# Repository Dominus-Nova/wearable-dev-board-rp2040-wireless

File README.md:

# wearable-dev-board-rp2040-wireless
E

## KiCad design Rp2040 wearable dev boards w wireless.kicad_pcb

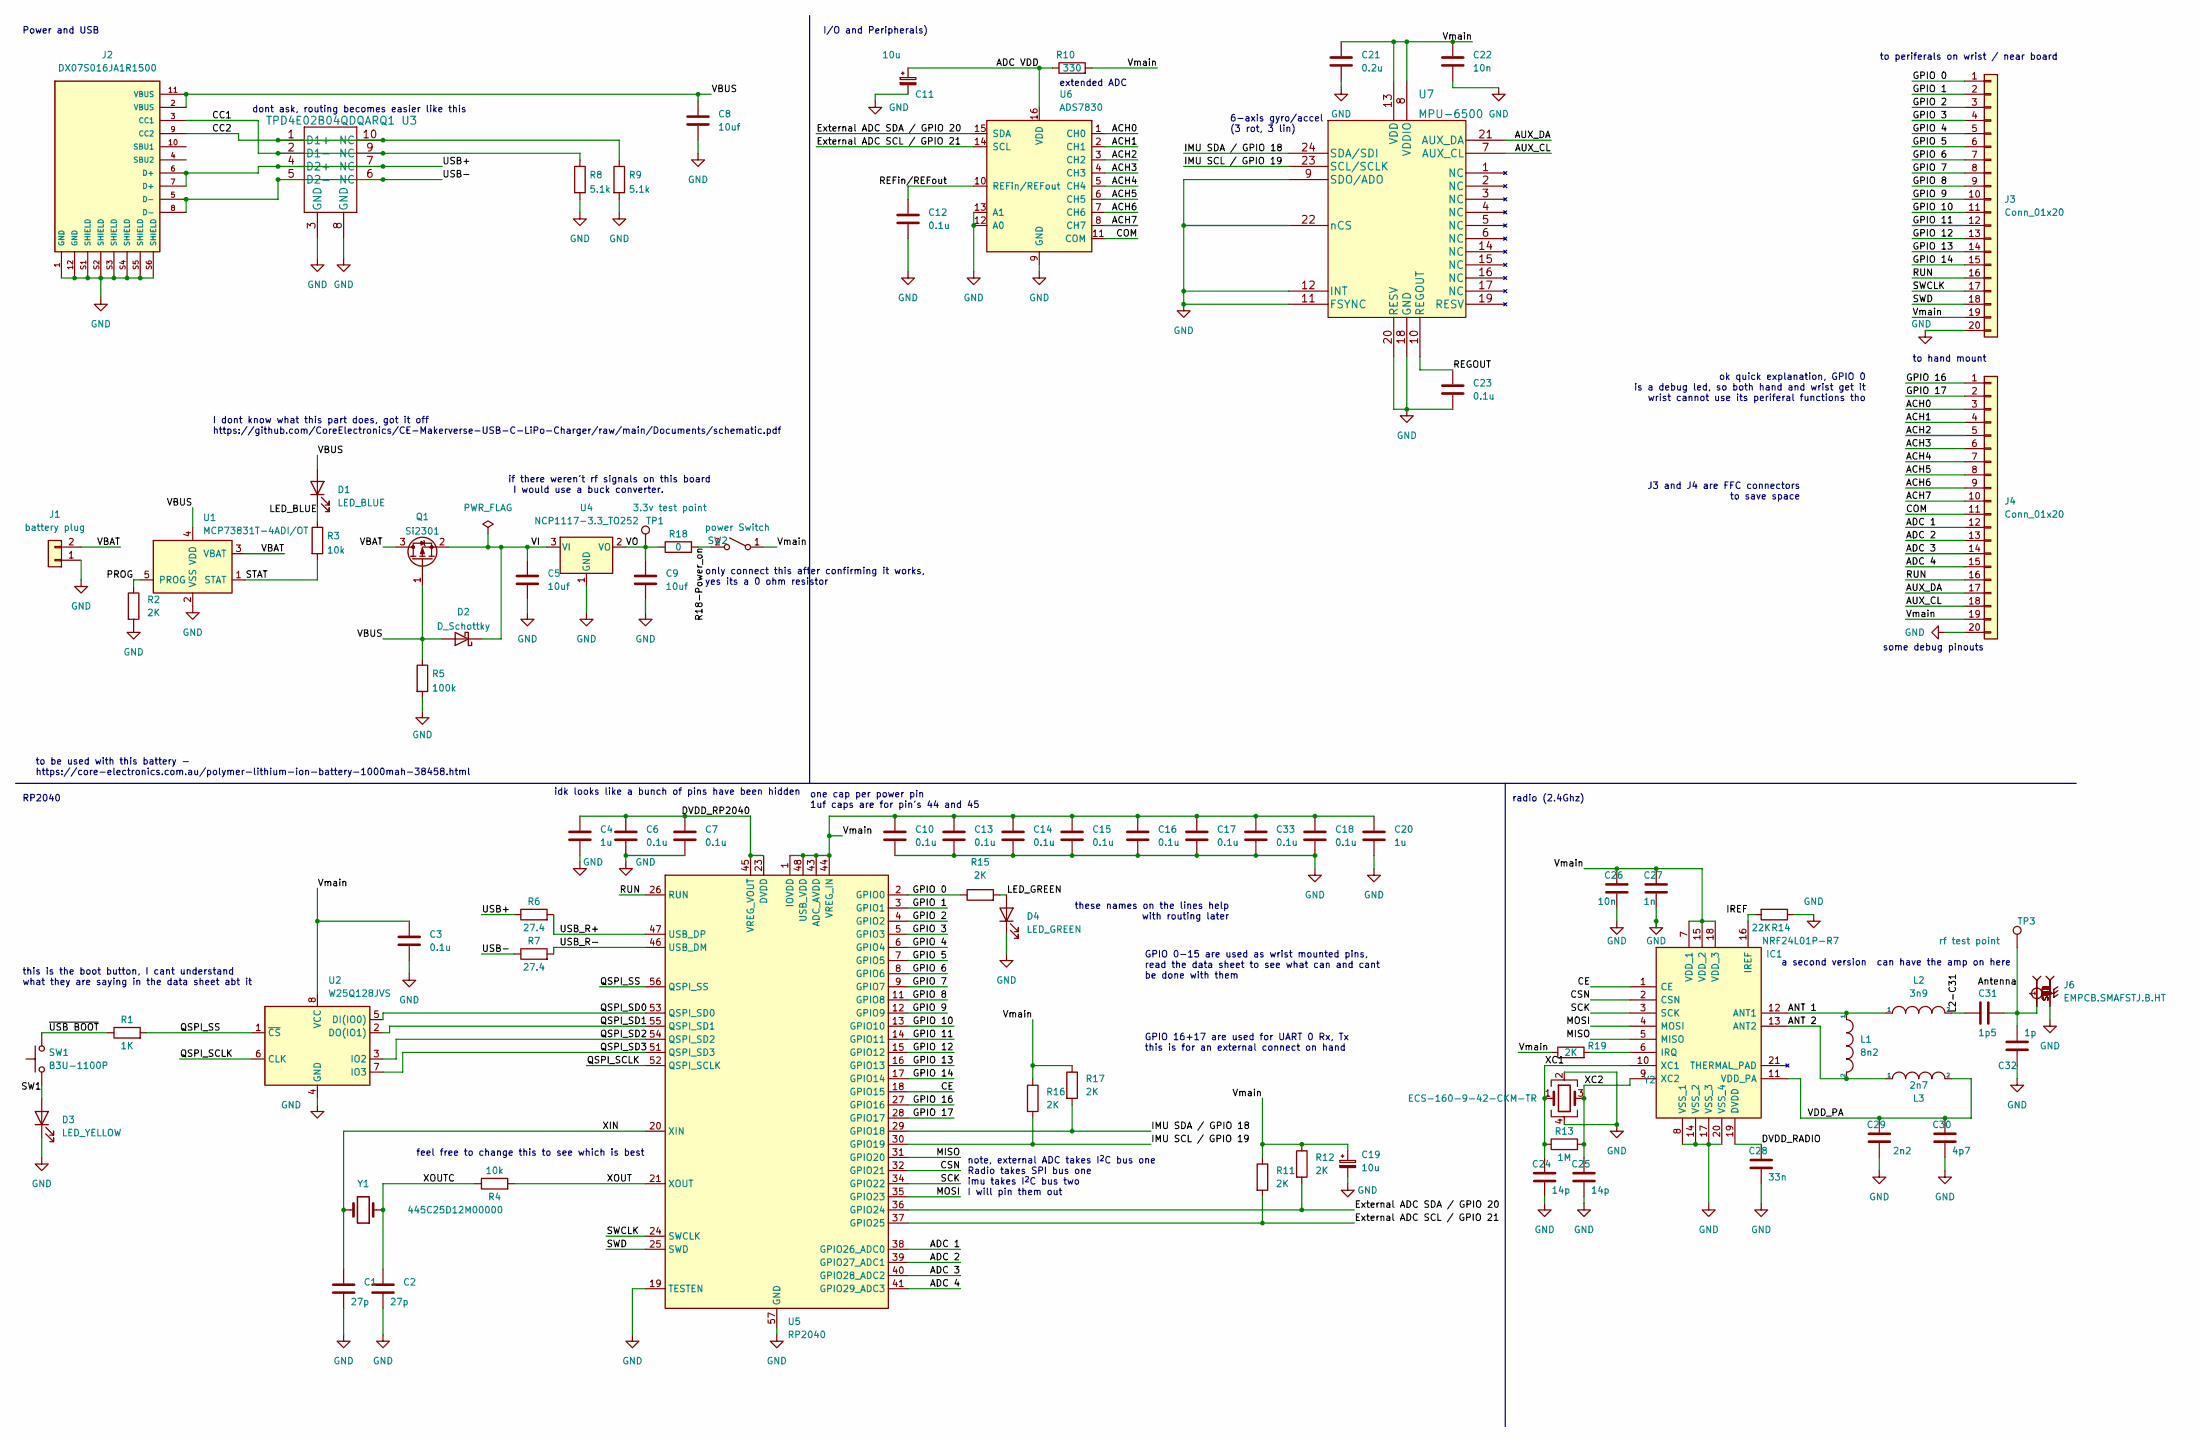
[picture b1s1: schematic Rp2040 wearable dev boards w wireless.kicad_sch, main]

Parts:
C1, C2: 27p; C_01005_0402Metric; Digikey Part Number 445-7173-6-ND
C3, C6, C7, C10, C12, C13, C14, C15, C16, C17, C18, C23, C33: 0.1u; C_0201_0603Metric; Digikey Part Number 490-3167-1-ND
C4, C20: 1u; C_0201_0603Metric; Digikey Part Number 478-7862-1-ND
C5, C8, C9: 10uf; C_0402_1005Metric; Digikey Part Number 490-GRM155R60J106ME05JCT-ND
C11, C19: 10u; CP_Elec_5x5.3; Digikey Part Number 732-6416-6-ND
C21: 0.2u; C_1206_3216Metric; Digikey Part Number 478-12814-1-ND
C22, C26: 10n; C_01005_0402Metric; Digikey Part Number 490-13319-1-ND
C24, C25: 14p; C_0402_1005Metric; Digikey Part Number 490-GJM1555C1H140FB01DCT-ND
C27: 1n; C_01005_0402Metric; Digikey Part Number 490-GRM022R71C102KE14LCT-ND
C28: 33n; C_01005_0402Metric; Digikey Part Number 490-9977-1-ND
C29: 2n2; C_01005_0402Metric; Digikey Part Number 490-7164-1-ND
C30: 4p7; C_01005_0402Metric; Digikey Part Number 490-13585-1-ND
C31: 1p5; C_01005_0402Metric; Digikey Part Number 490-13488-1-ND
C32: 1p; C_01005_0402Metric; Digikey Part Number 490-13474-1-ND
D1: LED_BLUE; LED_0603_1608Metric; Digikey Part Number 160-1827-1-ND
D2: D_Schottky; D_SMA; Digikey Part Number 641-1690-1-ND
D3: LED_YELLOW; LED_0603_1608Metric; Digikey Part Number 160-1448-1-ND
D4: LED_GREEN; LED_0603_1608Metric; Digikey Part Number 160-1446-1-ND
IC1: NRF24L01P-R7; QFN50P400X400X95-21N-D; Manufacturer_Part_Number NRF24L01P-R7; Mouser Part Number 949-NRF24L01P-R7
J1: battery plug; JST_PH_S2B-PH-SM4-TB_1x02-1MP_P2.00mm_Horizontal; Digikey Part Number 455-1749-1-ND
J2: DX07S016JA1R1500; JAE_DX07S016JA1R1500; PARTREV 1; Digikey Part Number 670-DX07S016JA1R1500CT-ND
J3, J4: Conn_01x20; TE_2-84952-0_1x20-1MP_P1.0mm_Horizontal; Digikey Part Number A100319CT-ND
J6: EMPCB.SMAFSTJ.B.HT; TAOGLAS_EMPCB.SMAFSTJ.B.HT; Digikey Part Number 931-1175-ND
L1: 8n2; L_0402_1005Metric; Digikey Part Number 490-6849-1-ND
L2: 3n9; L_0402_1005Metric; Digikey Part Number 490-6813-1-ND
L3: 2n7; L_0402_1005Metric; Digikey Part Number 490-6799-1-ND
Q1: Si2301; SOT-23; Digikey Part Number 353-SI2301A-TPCT-ND
R1: 1K; R_0402_1005Metric; Digikey Part Number 311-1.0KJRCT-ND
R2, R11, R12, R15, R16, R17, R19: 2K; R_0402_1005Metric; Digikey Part Number YAG2303CT-ND
R3, R4: 10k; R_0402_1005Metric; Digikey Part Number 311-10KJRCT-ND
R5: 100k; R_0402_1005Metric; Digikey Part Number 13-RC0402FR-13100KLCT-ND
R6, R7: 27.4; R_0402_1005Metric; Digikey Part Number YAG3085CT-ND
R8, R9: 5.1k; R_0402_1005Metric; Digikey Part Number 13-RC0402FR-135K1LCT-ND
R10: 330; R_0402_1005Metric; Digikey Part Number 311-330JRCT-ND
R13: 1M; R_0402_1005Metric; Digikey Part Number 311-1.0MJRCT-ND
R14: 22K; R_0402_1005Metric; Digikey Part Number 311-22.0KLRCT-ND
R18: 0; R_0402_1005Metric; Digikey Part Number 311-0.0LRCT-ND
SW1: B3U-1100P; SW_SPST_B3U-1100P; Digikey Part Number SW1021CT-ND
SW2: power Switch; JST_PH_S2B-PH-SM4-TB_1x02-1MP_P2.00mm_Horizontal; Digikey Part Number 455-1749-1-ND
TP1: 3.3v test point; TestPoint_Pad_D2.0mm; Digikey Part Number n/a
TP3: rf test point; TestPoint_Pad_D2.0mm; Digikey Part Number n/a
U1: MCP73831T-4ADI/OT; SOT-23-5; Digikey Part Number MCP73831T-4ADI/OTCT-ND
U2: W25Q128JVS; SOIC-8_5.23x5.23mm_P1.27mm; Digikey Part Number W25Q128JVSIMCT-ND
U3: TPD4E02B04QDQARQ1; Digikey Part Number 296-48995-1-ND
U4: NCP1117-3.3_TO252; SOT-223; Digikey Part Number NCP1117LPST33T3GOSCT-ND
U5: RP2040; QFN-56-1EP_7x7mm_P0.4mm_EP3.2x3.2mm; Digikey Part Number 2648-SC0914(13)CT-ND
U6: ADS7830; TSSOP-16_4.4x5mm_P0.65mm; Digikey Part Number 296-25899-1-ND
U7: MPU-6500; Digikey Part Number 1428-1011-1-ND
Y1: 445C25D12M00000; Crystal_SMD_5032-2Pin_5.0x3.2mm_HandSoldering; Digikey Part Number CTX1162CT-ND
Y2: ECS-160-9-42-CKM-TR; XTAL_ECS-160-9-42-CKM-TR; Digikey Part Number XC1611CT-ND

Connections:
/ACH0: J4.3, U6.1 (CH0)
/ACH1: J4.4, U6.2 (CH1)
/ACH2: J4.5, U6.3 (CH2)
/ACH3: J4.6, U6.4 (CH3)
/ACH4: J4.7, U6.5 (CH4)
/ACH5: J4.8, U6.6 (CH5)
/ACH6: J4.9, U6.7 (CH6)
/ACH7: J4.10, U6.8 (CH7)
/ADC 1: J4.12, U5.38 (GPIO26_ADC0)
/ADC 2: J4.13, U5.39 (GPIO27_ADC1)
/ADC 3: J4.14, U5.40 (GPIO28_ADC2)
/ADC 4: J4.15, U5.41 (GPIO29_ADC3)
/ADC VDD: C11.1, R10.1, U6.16 (VDD)
/ANT 1: IC1.12 (ANT1), L1.1, L2.1
/ANT 2: IC1.13 (ANT2), L1.2, L3.1
/AUX_CL: J4.18, U7.7 (AUX_CL)
/AUX_DA: J4.17, U7.21 (AUX_DA)
/Antenna: C31.2, C32.1, J6.1, TP3.1; also elsewhere on the board
/CC1: J2.3 (CC1), R8.1, U3.2 (D1-), U3.9 (NC)
/CC2: J2.9 (CC2), R9.1, U3.1 (D1+), U3.10 (NC)
/CE: IC1.1 (CE), U5.18 (GPIO15)
/COM: J4.11, U6.11 (COM)
/CSN: IC1.2 (CSN), U5.32 (GPIO21)
/DVDD_RADIO: C28.1, IC1.19 (DVDD)
/DVDD_RP2040: C4.1, C6.1, C7.1, U5.23 (DVDD), U5.45 (VREG_VOUT), U5.50 (DVDD)
/External ADC SCL / GPIO 21: R11.2, U5.37 (GPIO25), U6.14 (SCL)
/External ADC SDA / GPIO 20: R12.2, U5.36 (GPIO24), U6.15 (SDA)
/GPIO 0: J3.1, R15.1, U5.2 (GPIO0)
/GPIO 1: J3.2, U5.3 (GPIO1)
/GPIO 2: J3.3, U5.4 (GPIO2)
/GPIO 3: J3.4, U5.5 (GPIO3)
/GPIO 4: J3.5, U5.6 (GPIO4)
/GPIO 5: J3.6, U5.7 (GPIO5)
/GPIO 6: J3.7, U5.8 (GPIO6)
/GPIO 7: J3.8, U5.9 (GPIO7)
/GPIO 8: J3.9, U5.11 (GPIO8)
/GPIO 9: J3.10, U5.12 (GPIO9)
/GPIO 10: J3.11, U5.13 (GPIO10)
/GPIO 11: J3.12, U5.14 (GPIO11)
/GPIO 12: J3.13, U5.15 (GPIO12)
/GPIO 13: J3.14, U5.16 (GPIO13)
/GPIO 14: J3.15, U5.17 (GPIO14)
/GPIO 16: J4.1, U5.27 (GPIO16)
/GPIO 17: J4.2, U5.28 (GPIO17)
/IMU SCL / GPIO 19: R16.2, U5.30 (GPIO19), U7.23 (SCL/SCLK)
/IMU SDA / GPIO 18: R17.2, U5.29 (GPIO18), U7.24 (SDA/SDI)
/IREF: IC1.16 (IREF), R14.2
/L2-C31: C31.1, L2.2
/LED_BLUE: D1.1 (K), R3.1
/LED_GREEN: D4.2 (A), R15.2
/MISO: IC1.5 (MISO), U5.31 (GPIO20)
/MOSI: IC1.4 (MOSI), U5.35 (GPIO23)
/PROG: R2.1, U1.5 (PROG)
/QSPI_SCLK: U2.6 (CLK), U5.52 (QSPI_SCLK)
/QSPI_SD0: U2.5 (DI(IO0)), U5.53 (QSPI_SD0)
/QSPI_SD1: U2.2 (DO(IO1)), U5.55 (QSPI_SD1)
/QSPI_SD2: U2.3 (IO2), U5.54 (QSPI_SD2)
/QSPI_SD3: U2.7 (IO3), U5.51 (QSPI_SD3)
/QSPI_SS: R1.2, U2.1 (~CS), U5.56 (QSPI_SS)
/R18-Power_on: R18.2, SW2.2 (B)
/REFin/REFout: C12.1, U6.10 (REFin/REFout)
/REGOUT: C23.1, U7.10 (REGOUT)
/RUN: J3.16, J4.16, U5.26 (RUN)
/SCK: IC1.3 (SCK), U5.34 (GPIO22)
/STAT: R3.2, U1.1 (STAT)
/SW1: D3.2 (A), SW1.1
/SWCLK: J3.17, U5.24 (SWCLK)
/SWD: J3.18, U5.25 (SWD)
/USB+: J2.6 (D+), J2.7 (D+), R6.1, U3.4 (D2+), U3.7 (NC)
/USB-: J2.5 (D-), J2.8 (D-), R7.1, U3.5 (D2-), U3.6 (NC)
/USB_R+: R6.2, U5.47 (USB_DP)
/USB_R-: R7.2, U5.46 (USB_DM)
/VBAT: J1.2, Q1.3 (D), U1.3 (VBAT)
/VBUS: C8.1, D1.2 (A), D2.2 (A), J2.2 (VBUS), J2.11 (VBUS), Q1.1 (G), R5.1, U1.4 (VDD)
/VDD_PA: C29.1, C30.1, IC1.11 (VDD_PA), L3.2
/VI: C5.1, D2.1 (K), Q1.2 (S), U4.3 (VI)
/VO: C9.1, R18.1, TP1.1, U4.2 (VO)
/Vmain: C3.1, C10.1, C13.1, C14.1, C15.1, C16.1, C17.1, C18.1, C19.1, C20.1, C21.1, C22.1, C26.1, C27.1, C33.1, IC1.7 (VDD_1), IC1.15 (VDD_2), IC1.18 (VDD_3), J3.19, J4.19, R10.2, R11.1, R12.1, R16.1, R17.1, R19.1, SW2.1 (A), U2.8 (VCC), U5.1 (IOVDD), U5.10 (IOVDD), U5.22 (IOVDD), U5.33 (IOVDD), U5.42 (IOVDD), U5.43 (ADC_AVDD), U5.44 (VREG_IN), U5.48 (USB_VDD), U5.49 (IOVDD), U7.8 (VDDIO), U7.13 (VDD)
/XC1: C24.1, IC1.10 (XC1), R13.1, Y2.1
/XC2: C25.1, IC1.9 (XC2), R13.2, Y2.3
/XIN: C1.1, U5.20 (XIN), Y1.2
/XOUT: R4.2, U5.21 (XOUT)
/XOUTC: C2.1, R4.1, Y1.1
/~USB BOOT: R1.1, SW1.2
GND: C1.2, C2.2, C3.2, C4.2, C5.2, C6.2, C7.2, C8.2, C9.2, C10.2, C11.2, C12.2, C13.2, C14.2, C15.2, C16.2, C17.2, C18.2, C19.2, C20.2, C21.2, C22.2, C23.2, C24.2, C25.2, C26.2, C27.2, C28.2, C29.2, C30.2, C32.2, C33.2, D3.1 (K), D4.1 (K), IC1.8 (VSS_1), IC1.14 (VSS_2), IC1.17 (VSS_3), IC1.20 (VSS_4), J1.1, J2.1 (GND), J2.12 (GND), J2.S1 (SHIELD), J2.S2 (SHIELD), J2.S3 (SHIELD), J2.S4 (SHIELD), J2.S5 (SHIELD), J2.S6 (SHIELD), J3.20, J4.20, J6.SH1, J6.SH2, J6.SH3, J6.SH4, R2.2, R5.2, R8.2, R9.2, R14.1, U1.2 (VSS), U2.4 (GND), U3.3 (GND), U3.8 (GND), U4.1 (GND), U5.19 (TESTEN), U5.57 (GND), U6.9 (GND), U6.12 (A0), U6.13 (A1), U7.9 (SDO/ADO), U7.11 (FSYNC), U7.12 (INT), U7.18 (GND), U7.20 (RESV), U7.22 (nCS), Y2.2, Y2.4; also elsewhere on the board
unnamed: IC1.6 (IRQ), R19.2

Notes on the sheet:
I dont know what this part does, got it off https://github.com/CoreElectronics/CE-Makerverse-USB-C-LiPo-Charger/raw/main/Documents/schematic.pdf
6-axis gyro/accel (3 rot, 3 lin)
dont ask, routing becomes easier like this
radio (2.4Ghz)
if there weren't rf signals on this board I would use a buck converter.
note, external ADC takes I^{2}C bus one Radio takes SPI bus one imu takes I^{2}C bus two I will pin them out
this is the boot button, I cant understand what they are saying in the data sheet abt it
idk looks like a bunch of pins have been hidden
a second version can have the amp on here
extended ADC
I/O and Peripherals)
RP2040
these names on the lines help with routing later
GPIO 0-15 are used as wrist mounted pins, read the data sheet to see what can and cant be done with them
only connect this after confirming it works, yes its a 0 ohm resistor
some debug pinouts
to periferals on wrist / near board
one cap per power pin 1uf caps are for pin's 44 and 45
feel free to change this to see which is best
to be used with this battery - https://core-electronics.com.au/polymer-lithium-ion-battery-1000mah-38458.html
Power and USB
J3 and J4 are FFC connectors to save space
to hand mount
ok quick explanation, GPIO 0 is a debug led, so both hand and wrist get it wrist cannot use its periferal functions tho
GPIO 16+17 are used for UART 0 Rx, Tx this is for an external connect on hand

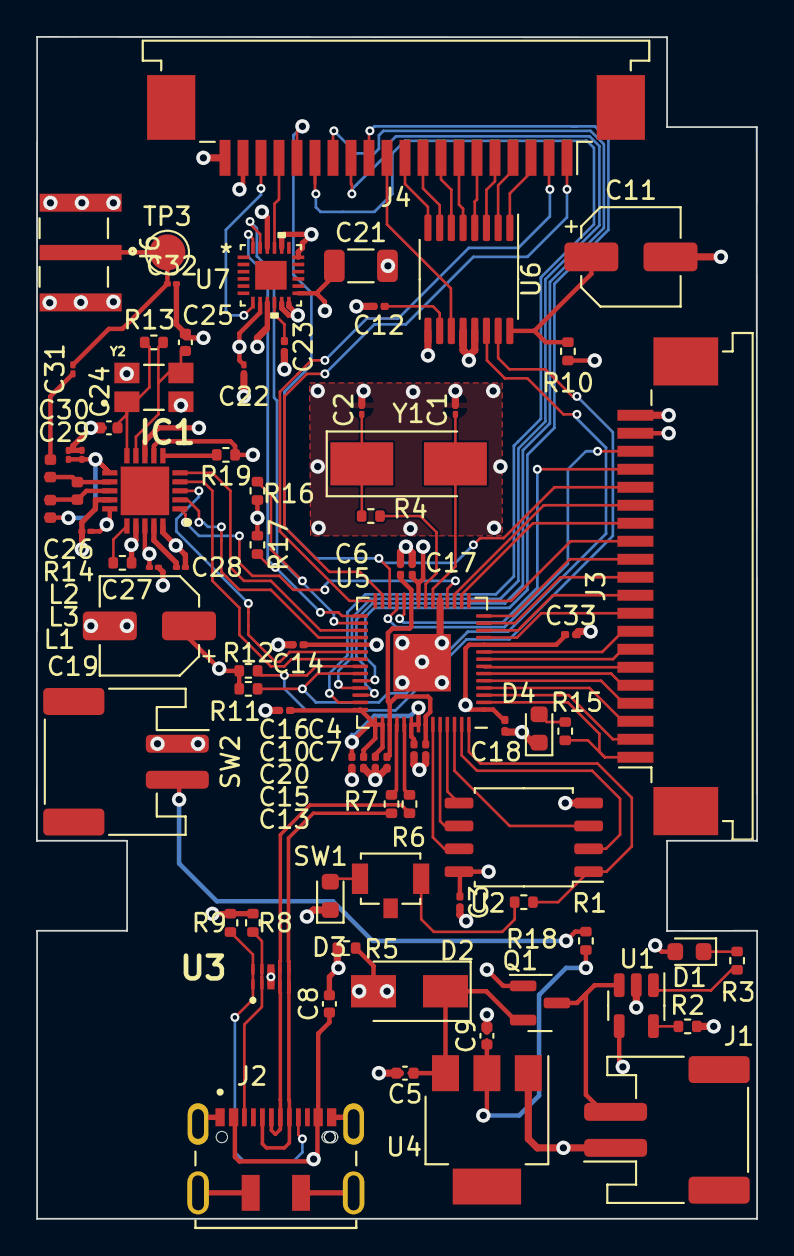
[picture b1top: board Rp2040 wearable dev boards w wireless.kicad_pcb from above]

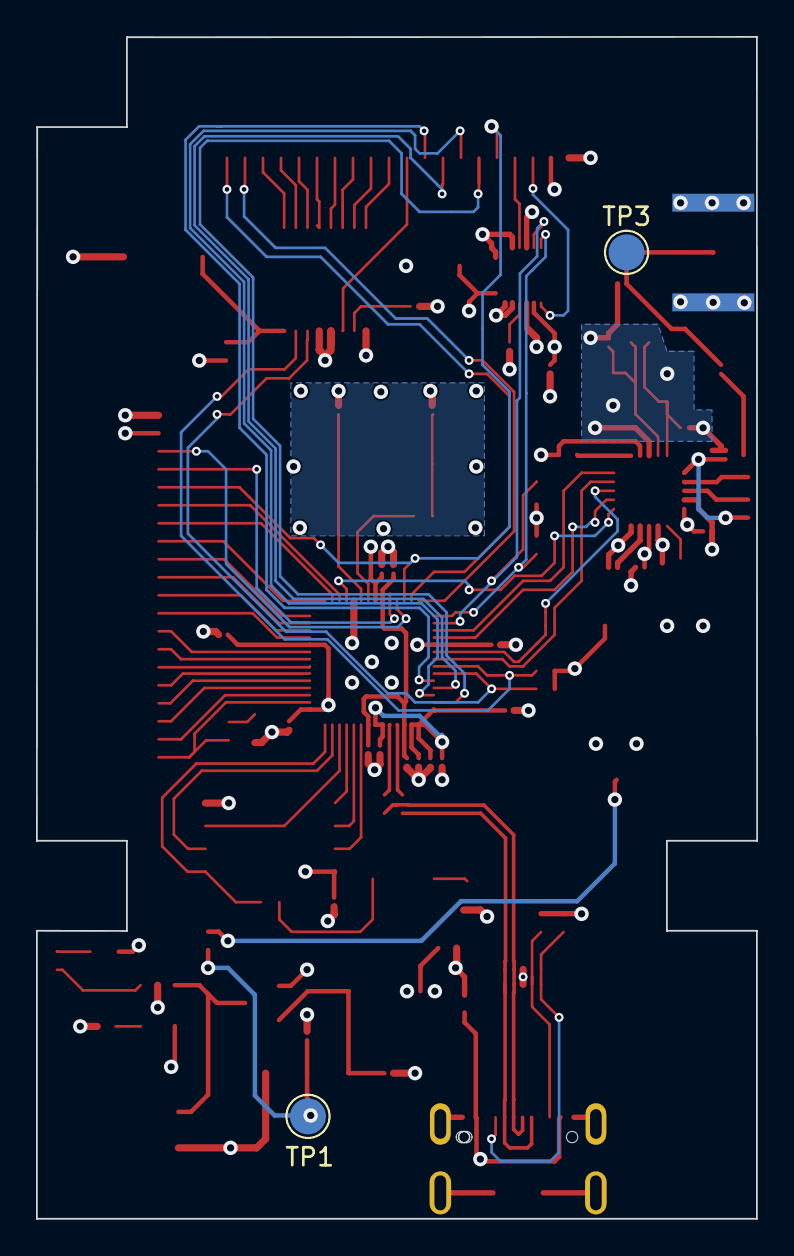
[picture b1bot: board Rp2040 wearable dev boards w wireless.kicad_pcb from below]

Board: 4 copper layers, 40.0 x 65.7 mm, 80 parts (2 on the bottom side), 86 nets.

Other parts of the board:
TP3#2: rf test point; TestPoint_Pad_D2.0mm

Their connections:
/Antenna: TP3#2.1; also elsewhere on the board
GND: TP3#2.1; also elsewhere on the board

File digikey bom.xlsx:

Item | Item | Item | Item | Item | Item | Item | Item | Item | Item | Item
1 | 2 | C1, C2 | 27p | Device:C | Capacitor_SMD:C_01005_0402Metric | ~ |  |  |  | 445-7173-6-ND
2 | 13 | C3, C6, C7, C10, C12, C13, C14, C15, C16, C17, C18, C23, C33 | 0.1u | Device:C | Capacitor_SMD:C_0201_0603Metric | ~ |  |  |  | 490-3167-1-ND
3 | 2 | C4, C20 | 1u | Device:C | Capacitor_SMD:C_0201_0603Metric | ~ |  |  |  | 478-7862-1-ND
4 | 3 | C5, C8, C9 | 10uf | Device:C | Capacitor_SMD:C_0402_1005Metric | ~ |  |  |  | 490-GRM155R60J106ME05JCT-ND
5 | 2 | C11, C19 | 10u | Device:C_Polarized_Small | Capacitor_SMD:CP_Elec_5x5.3 | ~ |  |  |  | 732-6416-6-ND
6 | 1 | C21 | 0.2u | Device:C | Capacitor_SMD:C_1206_3216Metric | ~ |  |  |  | 478-12814-1-ND
7 | 2 | C22, C26 | 10n | Device:C | Capacitor_SMD:C_01005_0402Metric | ~ |  |  |  | 490-13319-1-ND
8 | 2 | C24, C25 | 14p | Device:C | Capacitor_SMD:C_0402_1005Metric | ~ |  |  |  | 490-GJM1555C1H140FB01DCT-ND
9 | 1 | C27 | 1n | Device:C | Capacitor_SMD:C_01005_0402Metric | ~ |  |  |  | 490-GRM022R71C102KE14LCT-ND
10 | 1 | C28 | 33n | Device:C | Capacitor_SMD:C_01005_0402Metric | ~ |  |  |  | 490-9977-1-ND
11 | 1 | C29 | 2n2 | Device:C | Capacitor_SMD:C_01005_0402Metric | ~ |  |  |  | 490-7164-1-ND
12 | 1 | C30 | 4p7 | Device:C | Capacitor_SMD:C_01005_0402Metric | ~ |  |  |  | 490-13585-1-ND
13 | 1 | C31 | 1p5 | Device:C | Capacitor_SMD:C_01005_0402Metric | ~ |  |  |  | 490-13488-1-ND
14 | 1 | C32 | 1p | Device:C | Capacitor_SMD:C_01005_0402Metric | ~ |  |  |  | 490-13474-1-ND
15 | 1 | D1 | LED_BLUE | Device:LED | LED_SMD:LED_0603_1608Metric | ~ |  |  |  | 160-1827-1-ND
16 | 1 | D2 | D_Schottky | Device:D_Schottky | Diode_SMD:D_SMA | ~ |  |  |  | 641-1690-1-ND
17 | 1 | D3 | LED_YELLOW | Device:LED | LED_SMD:LED_0603_1608Metric | ~ |  |  |  | 160-1448-1-ND
18 | 1 | D4 | LED_GREEN | Device:LED | LED_SMD:LED_0603_1608Metric | ~ |  |  |  | 160-1446-1-ND
19 | 1 | IC1 | NRF24L01P-R7 | NRF24L01P-R7:NRF24L01P-R7 | LIB_NRF24L01P-R7:QFN50P400X400X95-21N-D | https://www.mouser.com/ds/2/297/nRF24L01P-1187709.pdf | NRF24L01P-R7 | https://www.arrow.com/en/products/nrf24l01p-r7/nordic-semico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 | NORDIC SEMICONDUCTOR - NRF24L01P-R7 - RF TRANSCEIVER, 2MBPS, 2.525GHZ, QFN-20 | 1490-1033-1-ND
20 | 1 | J1 | battery plug | Connector_Generic:Conn_01x02 | Connector_JST:JST_PH_S2B-PH-SM4-TB_1x02-1MP_P2.00mm_Horizontal | https://core-electronics.com.au/polymer-lithium-ion-battery-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 |  |  |  | 455-1749-1-ND
21 | 1 | J2 | DX07S016JA1R1500 | usb-c usb 2.0:DX07S016JA1R1500 | JAE_DX07S016JA1R1500 |  |  |  |  | 670-DX07S016JA1R1500CT-ND
22 | 2 | J3, J4 | Conn_01x20 | Connector_Generic:Conn_01x20 | Connector_FFC-FPC:TE_2-84952-0_1x20-1MP_P1.0mm_Horizontal | https://www.te.com/commerce/DocumentDelivery/DDEController?A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 |  |  |  | A100319CT-ND
23 | 1 | J6 | EMPCB.SMAFSTJ.B.HT | EMPCB.SMAFSTJ.B.HT:EMPCB.SMAFSTJ.B.HT | TAOGLAS_EMPCB.SMAFSTJ.B.HT |  |  |  |  | 931-1175-ND
24 | 1 | L1 | 8n2 | pspice:INDUCTOR | Inductor_SMD:L_0402_1005Metric | ~ |  |  |  | 490-6849-1-ND
25 | 1 | L2 | 3n9 | pspice:INDUCTOR | Inductor_SMD:L_0402_1005Metric | ~ |  |  |  | 490-6813-1-ND
26 | 1 | L3 | 2n7 | pspice:INDUCTOR | Inductor_SMD:L_0402_1005Metric | ~ |  |  |  | 490-6799-1-ND
27 | 1 | Q1 | Si2301 | Device:Q_PMOS_GSD | Package_TO_SOT_SMD:SOT-23 | ~ |  |  |  | 353-SI2301A-TPCT-ND
28 | 1 | R1 | 1K | Device:R | Resistor_SMD:R_0402_1005Metric | ~ |  |  |  | 311-1.0KJRCT-ND
29 | 7 | R2, R11, R12, R15, R16, R17, R19 | 2K | Device:R | Resistor_SMD:R_0402_1005Metric | ~ |  |  |  | YAG2303CT-ND
30 | 2 | R3, R4 | 10k | Device:R | Resistor_SMD:R_0402_1005Metric | ~ |  |  |  | 311-10KJRCT-ND
31 | 1 | R5 | 100k | Device:R | Resistor_SMD:R_0402_1005Metric | ~ |  |  |  | 13-RC0402FR-13100KLCT-ND
32 | 2 | R6, R7 | 27.4 | Device:R | Resistor_SMD:R_0402_1005Metric | ~ |  |  |  | YAG3085CT-ND
33 | 2 | R8, R9 | 5.1k | Device:R | Resistor_SMD:R_0402_1005Metric | ~ |  |  |  | 13-RC0402FR-135K1LCT-ND
34 | 1 | R10 | 330 | Device:R | Resistor_SMD:R_0402_1005Metric | ~ |  |  |  | 311-330JRCT-ND
35 | 1 | R13 | 1M | Device:R | Resistor_SMD:R_0402_1005Metric | ~ |  |  |  | 311-1.0MJRCT-ND
36 | 1 | R14 | 22K | Device:R | Resistor_SMD:R_0402_1005Metric | ~ |  |  |  | 311-22.0KLRCT-ND
37 | 1 | R18 | 0 | Device:R | Resistor_SMD:R_0402_1005Metric | ~ |  |  |  | 311-0.0LRCT-ND
38 | 1 | SW1 | B3U-1100P | Switch:SW_Push | Button_Switch_SMD:SW_SPST_B3U-1100P | ~ |  |  |  | SW1021CT-ND
39 | 1 | SW2 | power Switch | Switch:SW_SPST | Connector_JST:JST_PH_S2B-PH-SM4-TB_1x02-1MP_P2.00mm_Horizontal | ~ |  |  |  | 455-1749-1-ND
40 | 1 | TP1 | 3.3v test point | Connector:TestPoint | TestPoint:TestPoint_Pad_D2.0mm | ~ |  |  |  | n/a
41 | 1 | TP3 | rf test point | Connector:TestPoint | TestPoint:TestPoint_Pad_D2.0mm | ~ |  |  |  | n/a
42 | 1 | U1 | MCP73831T-4ADI/OT | Battery_Management:MCP73832-2-OT | Package_TO_SOT_SMD:SOT-23-5 | http://ww1.microchip.com/downloads/en/DeviceDoc/20001984g.pdf |  |  |  | MCP73831T-4ADI/OTCT-ND
43 | 1 | U2 | W25Q128JVS | Memory_Flash:W25Q128JVS | Package_SO:SOIC-8_5.23x5.23mm_P1.27mm | http://www.winbond.com/resource-files/w25q128jv_dtr%20revc%2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 |  |  |  | W25Q128JVSIMCT-ND
44 | 1 | U3 | TPD4E02B04QDQARQ1 | TPD4E02B04QDQARQ1:TPD4E02B04QDQARQ1 | LIB_TPD4E02B04QDQARQ1:TPD4E02B04QDQARQ1 |  |  |  |  | 296-48995-1-ND
45 | 1 | U4 | NCP1117-3.3_TO252 | Regulator_Linear:NCP1117-3.3_TO252 | Package_TO_SOT_SMD:SOT-223 | http://www.onsemi.com/pub_link/Collateral/NCP1117-D.PDF |  |  |  | NCP1117LPST33T3GOSCT-ND
46 | 1 | U5 | RP2040 | MCU_RaspberryPi:RP2040 | Package_DFN_QFN:QFN-56-1EP_7x7mm_P0.4mm_EP3.2x3.2mm | https://datasheets.raspberrypi.com/rp2040/rp2040-datasheet.pdf |  |  |  | 2648-SC0914(13)CT-ND
47 | 1 | U6 | ADS7830 | Analog_DAC:ADS7830 | Package_SO:TSSOP-16_4.4x5mm_P0.65mm | http://www.ti.com/lit/ds/symlink/ads7830.pdf |  |  |  | 296-25899-1-ND
48 | 1 | U7 | MPU-6500 | MPU-6500:MPU-6500 | MPU-6500:MPU-6500 |  |  |  |  | 1428-1011-1-ND
49 | 1 | Y1 | 445C25D12M00000 | Device:Crystal | Crystal:Crystal_SMD_5032-2Pin_5.0x3.2mm_HandSoldering | ~ |  |  |  | CTX1162CT-ND
50 | 1 | Y2 | ECS-160-9-42-CKM-TR | Device:Crystal_GND24 | ECS-160-9-42-CKM-TR:XTAL_ECS-160-9-42-CKM-TR | ~ |  |  |  | XC1611CT-ND

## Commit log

2022-11-17 started work on adc
2022-11-17 yeh, stuff happened finished rp2040 pinout, added the IMU that is going to be used, created a set of solder pads (x21) for the GPIO
2022-11-17 created readme
2022-11-17 finnished preiferals added names and pads
2022-11-18 finished schematic v.1 about to start routing
2022-11-18 finished schematic started pcb design, will need to review the power section.
2022-11-19 mmmmmmmmmmm change log.exe
2022-11-19 routed power
2022-11-20 started pinning out Rp2040 shortened board to 60 something long
2022-11-23 finished pcb route v1, asked the electronics discord if they could verify it.
2022-11-24 finished cap bom, need to reroute part of it to fit cap sizes
2022-11-26 more bom creation
2022-11-29 finished
2023-02-03 uhhh forgot to do this for a while, this was the first manufactured prototype
